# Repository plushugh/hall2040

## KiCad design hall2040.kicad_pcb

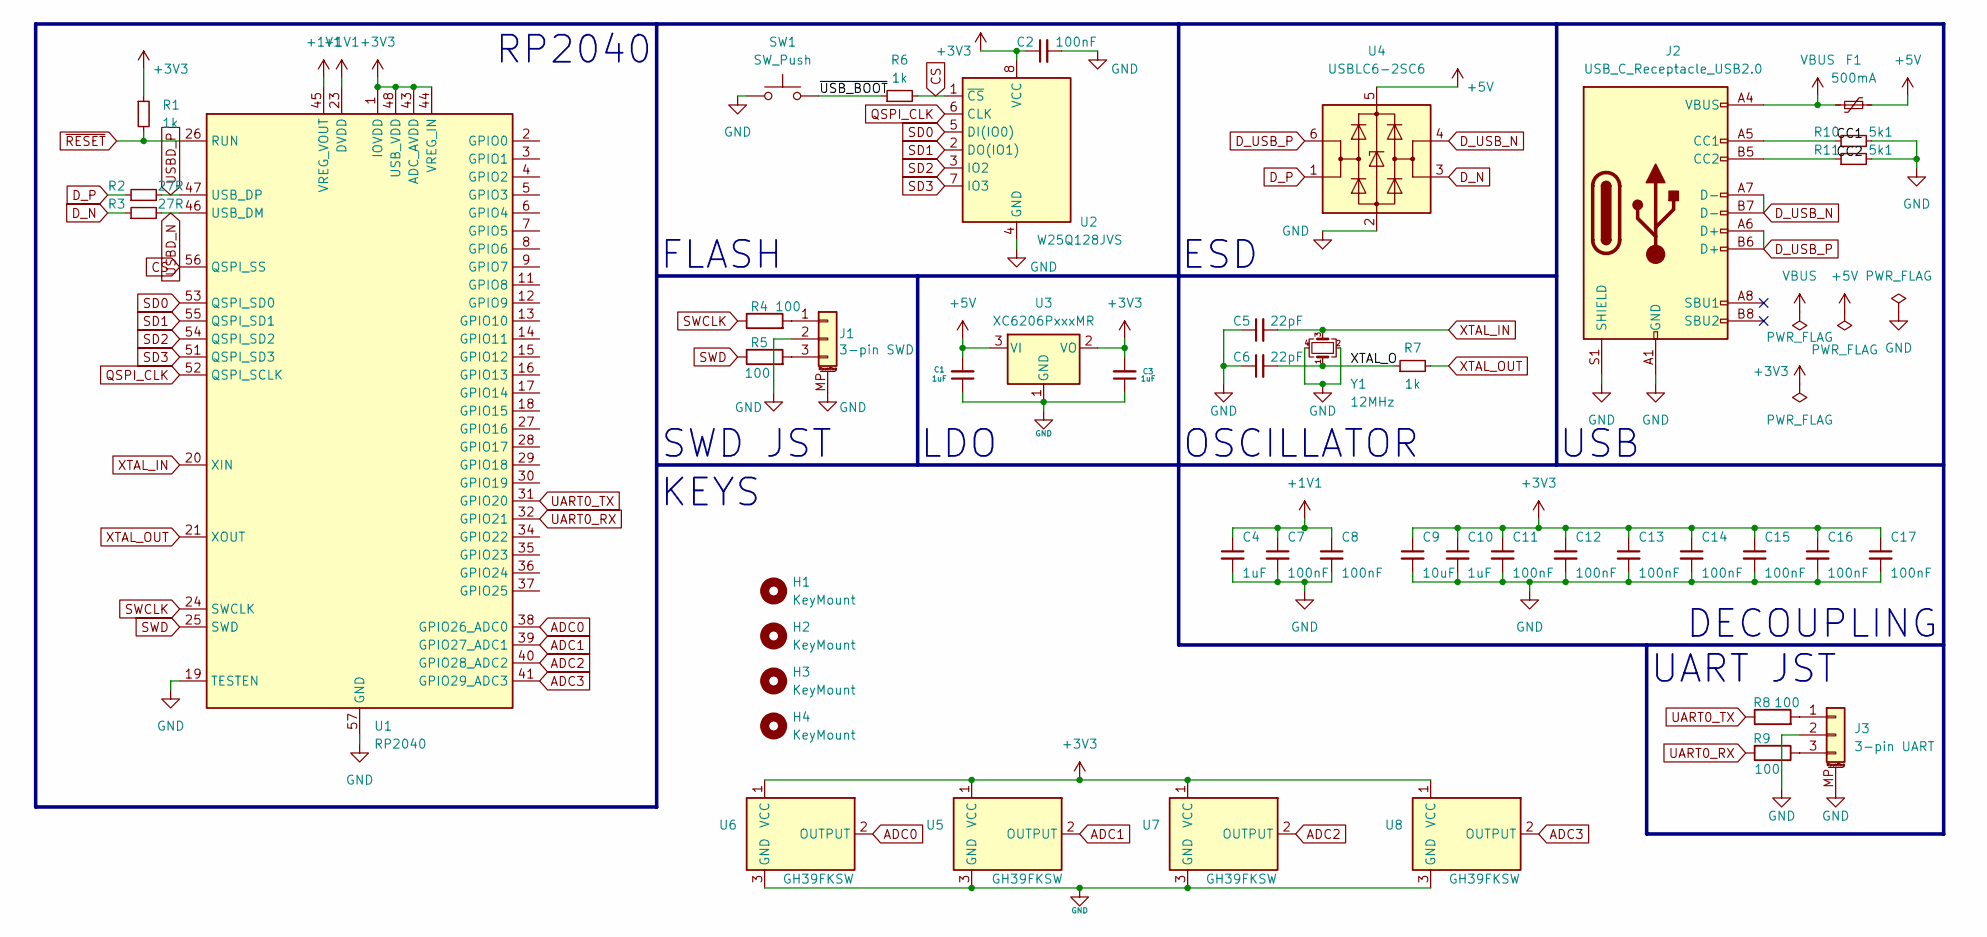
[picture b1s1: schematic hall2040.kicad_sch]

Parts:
C1, C3, C4, C10: 1uF; C_0402_1005Metric; LCSC C52923
C2, C7, C8, C11, C12, C13, C14, C15, C16, C17: 100nF; C_0402_1005Metric; LCSC C1525
C5, C6: 22pF; C_0402_1005Metric; LCSC C1555
C9: 10uF; C_0402_1005Metric; LCSC C15525
F1: 500mA; Fuse_1206_3216Metric; LCSC C70076
H1, H2, H3, H4: KeyMount; SW_Cherry_MX_PCB
J1: 3-pin SWD; JST_SH_BM03B-SRSS-TB_1x03-1MP_P1.00mm_Vertical
J2: USB_C_Receptacle_USB2.0; USB_C_Receptacle_HRO_TYPE-C-31-M-12; LCSC C165948
J3: 3-pin UART; JST_SH_BM03B-SRSS-TB_1x03-1MP_P1.00mm_Vertical
R1, R6, R7: 1k; R_0402_1005Metric; LCSC C11702
R2, R3: 27R; R_0603_1608Metric; LCSC C25190
R4, R5, R8, R9: 100; R_0603_1608Metric
R10, R11: 5k1; R_0402_1005Metric; LCSC C25905
SW1: SW_Push; SW_SPST_PTS810; LCSC C221896
U1: RP2040; QFN-56-1EP_7x7mm_P0.4mm_EP3.2x3.2mm; LCSC C2040
U2: W25Q128JVS; SOIC-8_5.23x5.23mm_P1.27mm; LCSC C131025
U3: XC6206PxxxMR; SOT-23-3; LCSC C5250982
U4: USBLC6-2SC6; SOT-23-6; LCSC C2827654
U5, U6, U7, U8: GH39FKSW; SOT-23; LCSC C266230
Y1: 12MHz; Crystal_SMD_3225-4Pin_3.2x2.5mm; LCSC C9002

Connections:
+1V1: C4.1, C7.1, C8.1, U1.23 (DVDD), U1.45 (VREG_VOUT), U1.50 (DVDD)
+3V3: C2.1, C3.2, C9.1, C10.1, C11.1, C12.1, C13.1, C14.1, C15.1, C16.1, C17.1, R1.1, U1.1 (IOVDD), U1.10 (IOVDD), U1.22 (IOVDD), U1.33 (IOVDD), U1.42 (IOVDD), U1.43 (ADC_AVDD), U1.44 (VREG_IN), U1.48 (USB_VDD), U1.49 (IOVDD), U2.8 (VCC), U3.2 (VO), U5.1 (VCC), U6.1 (VCC), U7.1 (VCC), U8.1 (VCC)
+5V: C1.2, F1.2, U3.3 (VI), U4.5 (VBUS)
/CC1: J2.A5 (CC1), R10.1
/CC2: J2.B5 (CC2), R11.1
/XTAL_O: C6.2, R7.1, Y1.1
/~USB_BOOT: R6.1, SW1.2
ADC0: U1.38 (GPIO26_ADC0), U6.2 (OUTPUT)
ADC1: U1.39 (GPIO27_ADC1), U5.2 (OUTPUT)
ADC2: U1.40 (GPIO28_ADC2), U7.2 (OUTPUT)
ADC3: U1.41 (GPIO29_ADC3), U8.2 (OUTPUT)
CS: R6.2, U1.56 (QSPI_SS), U2.1 (~CS)
D_N: R3.1, U4.3 (I/O2)
D_P: R2.1, U4.1 (I/O1)
D_USB_N: J2.A7 (D-), J2.B7 (D-), U4.4 (I/O2)
D_USB_P: J2.A6 (D+), J2.B6 (D+), U4.6 (I/O1)
GND: C1.1, C2.2, C3.1, C4.2, C5.1, C6.1, C7.2, C8.2, C9.2, C10.2, C11.2, C12.2, C13.2, C14.2, C15.2, C16.2, C17.2, J1.2, J1.MP (MountPin), J2.A1 (GND), J2.A12 (GND), J2.B1 (GND), J2.B12 (GND), J2.S1 (SHIELD), J3.2, J3.MP (MountPin), R10.2, R11.2, SW1.1, U1.19 (TESTEN), U1.57 (GND), U2.4 (GND), U3.1 (GND), U4.2 (GND), U5.3 (GND), U6.3 (GND), U7.3 (GND), U8.3 (GND), Y1.2, Y1.4
unnamed: J1.1, R4.2
unnamed: J1.3, R5.2
unnamed: J3.1, R8.2
unnamed: J3.3, R9.1
QSPI_CLK: U1.52 (QSPI_SCLK), U2.6 (CLK)
SD0: U1.53 (QSPI_SD0), U2.5 (DI(IO0))
SD1: U1.55 (QSPI_SD1), U2.2 (DO(IO1))
SD2: U1.54 (QSPI_SD2), U2.3 (IO2)
SD3: U1.51 (QSPI_SD3), U2.7 (IO3)
SWCLK: R4.1, U1.24 (SWCLK)
SWD: R5.1, U1.25 (SWD)
UART0_RX: R9.2, U1.32 (GPIO21)
UART0_TX: R8.1, U1.31 (GPIO20)
USBD_N: R3.2, U1.46 (USB_DM)
USBD_P: R2.2, U1.47 (USB_DP)
VBUS: F1.1, J2.A4 (VBUS), J2.A9 (VBUS), J2.B4 (VBUS), J2.B9 (VBUS)
XTAL_IN: C5.2, U1.20 (XIN), Y1.3
XTAL_OUT: R7.2, U1.21 (XOUT)
~RESET: R1.2, U1.26 (RUN)

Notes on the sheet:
RP2040
OSCILLATOR
ESD
UART JST
DECOUPLING
KEYS
SWD JST
USB
LDO
FLASH

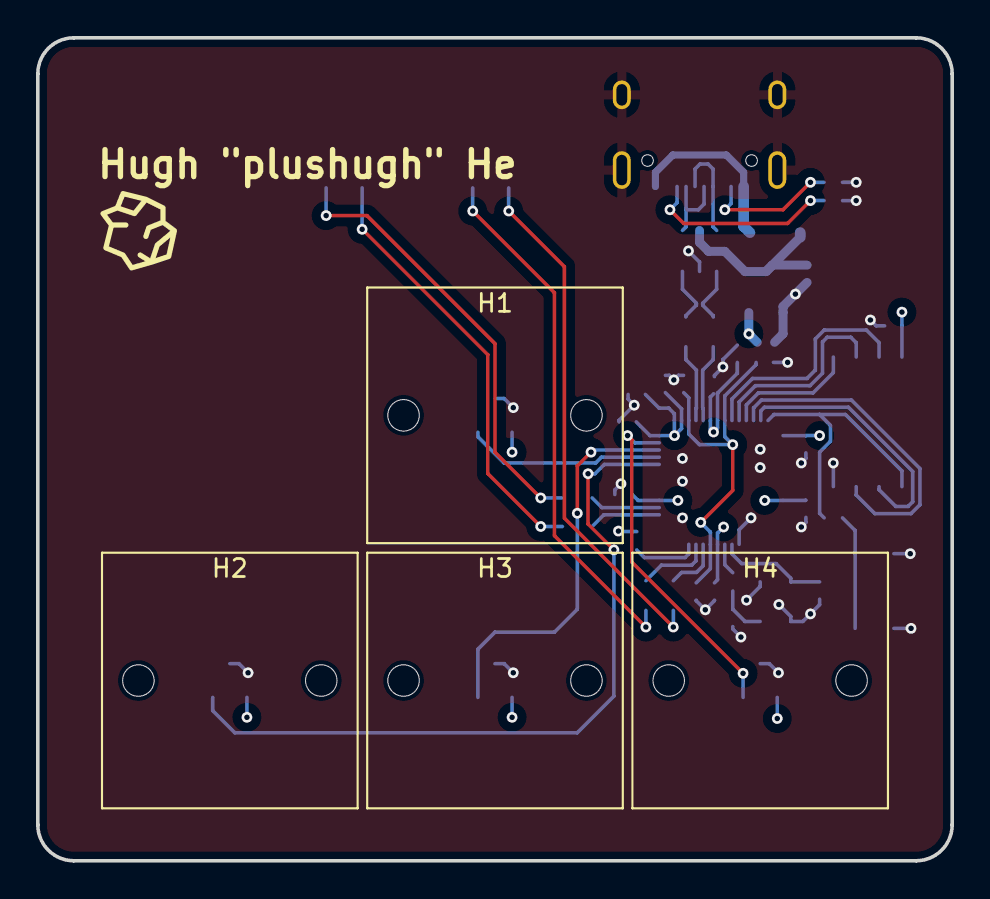
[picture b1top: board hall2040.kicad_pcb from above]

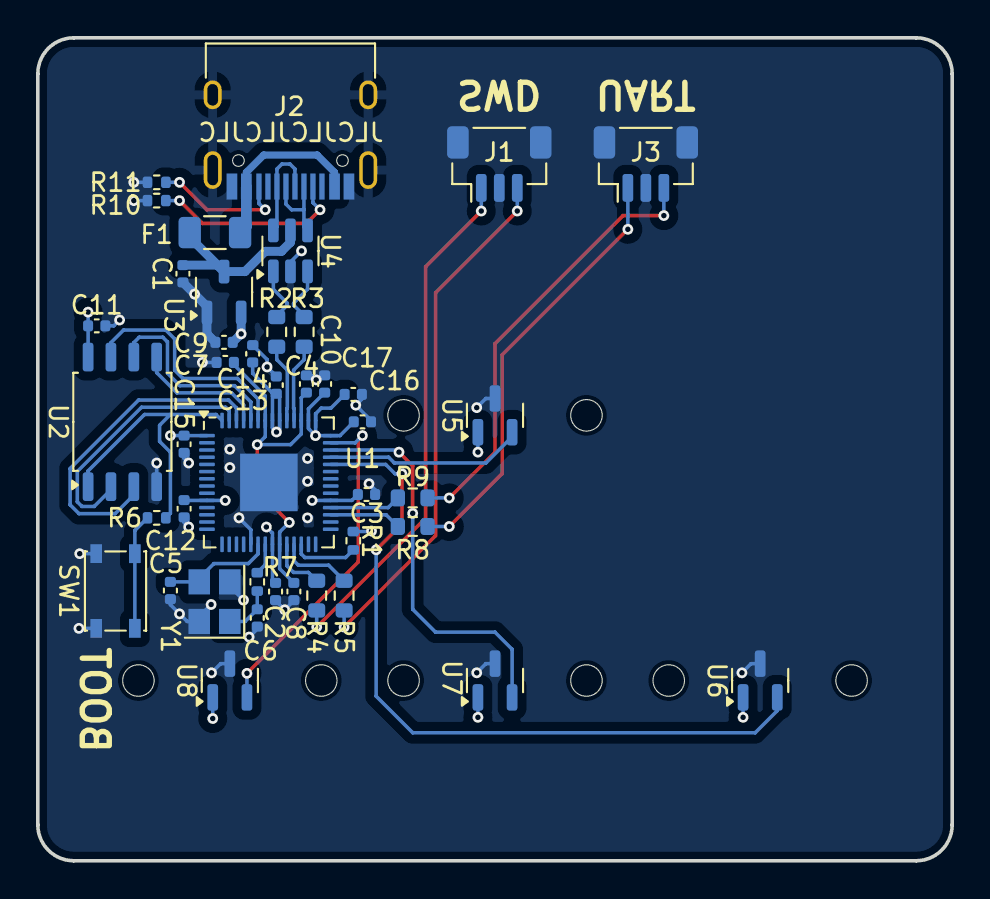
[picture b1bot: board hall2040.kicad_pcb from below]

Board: 4 copper layers, 50.8 x 45.7 mm, 46 parts (42 on the bottom side), 36 nets.

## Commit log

2024-03-05 feat: add files via upload
